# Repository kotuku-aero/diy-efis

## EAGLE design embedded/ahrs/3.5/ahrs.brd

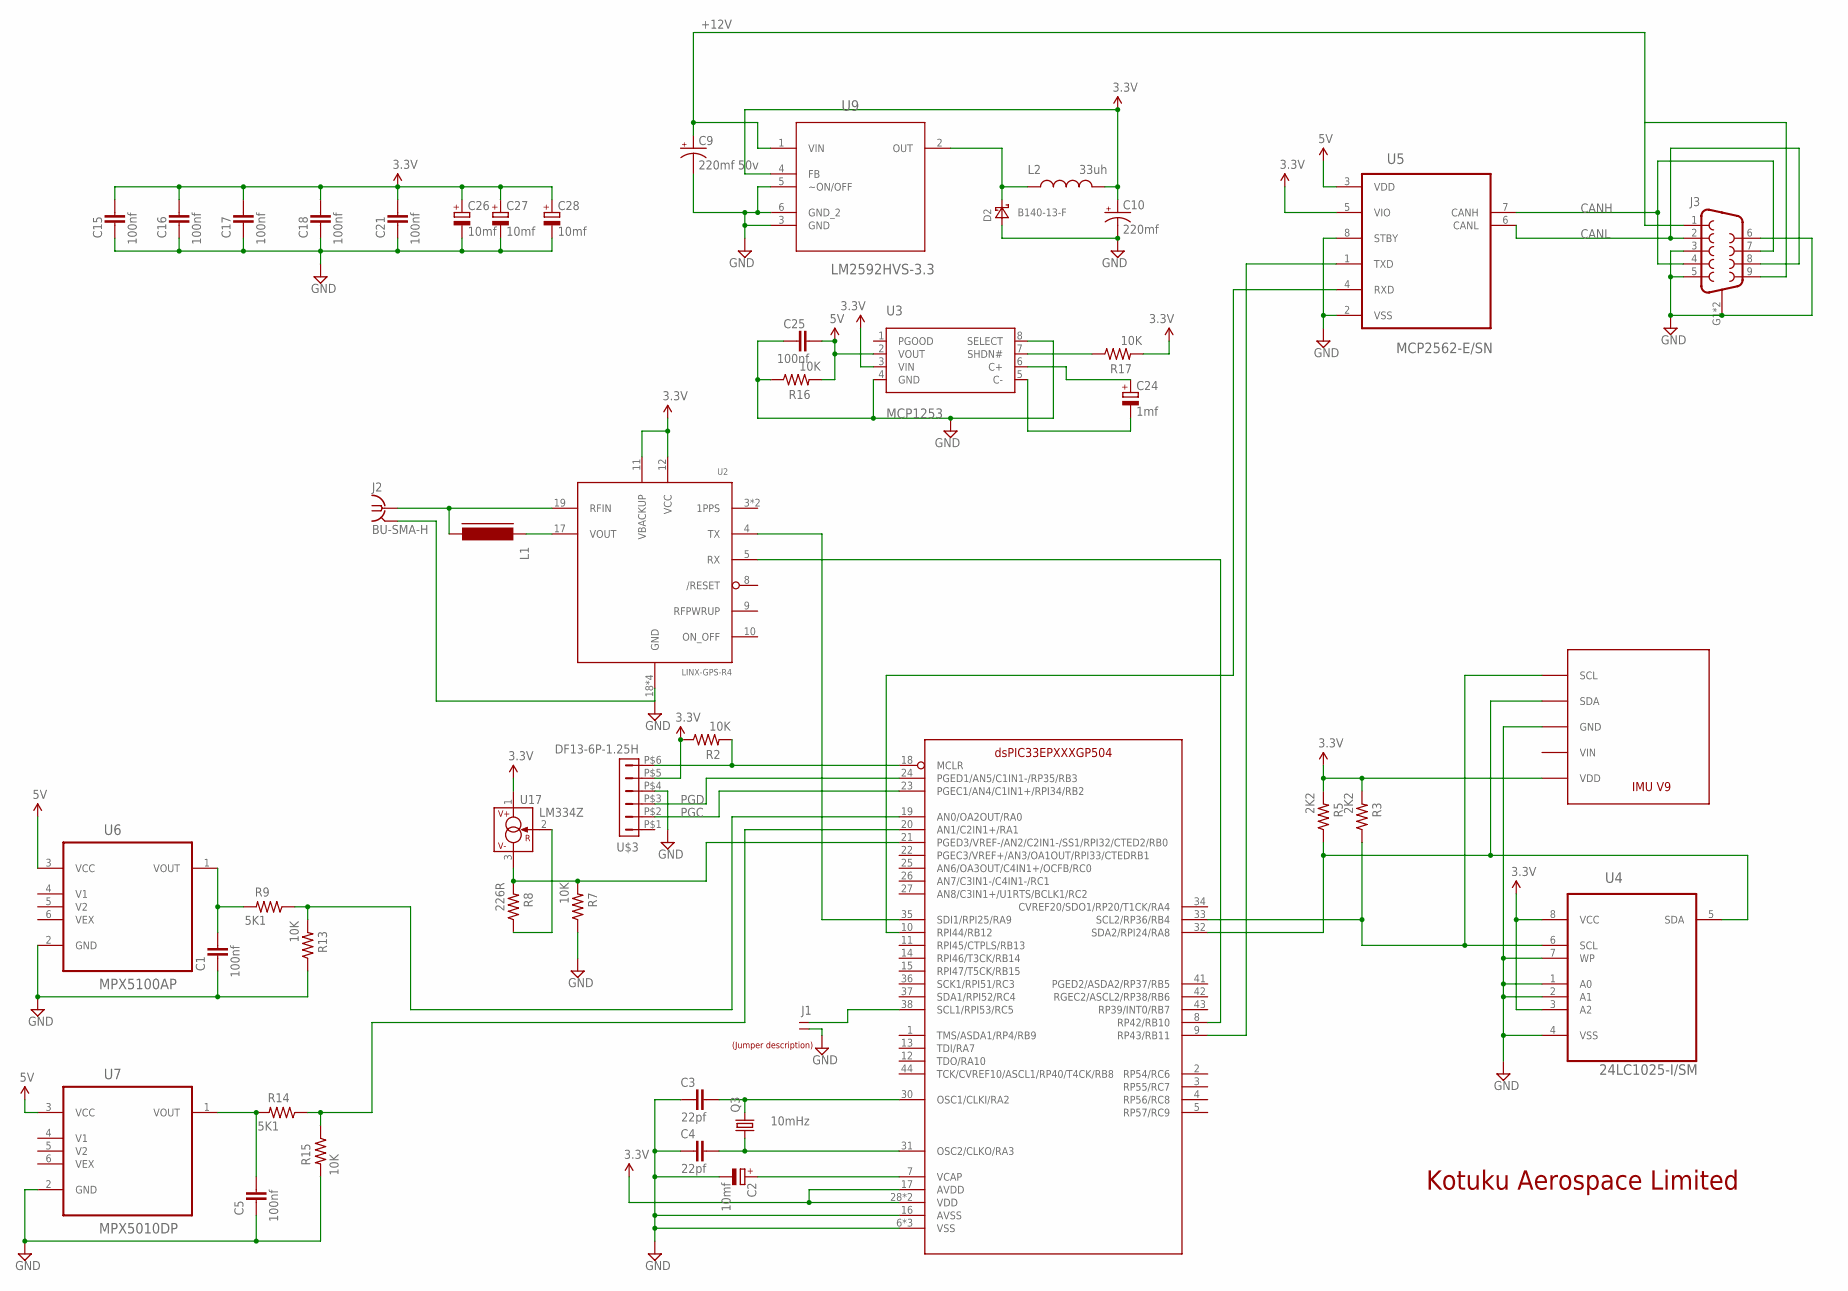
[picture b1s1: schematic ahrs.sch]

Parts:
C1, C5, C15, C16, C17, C18, C21, C25: 100nf; C805
C2, C26, C27, C28: 10mf; SMC_A
C3, C4: 22pf; C805
C9: 220mf 50v; EIA7343
C10: 220mf; EIA7343
C24: 1mf; SMC_A
D2: B140-13-F; SMA
J1: JUMPER-1X2
J2: BU-SMA-H; PARTNO 5-1814400-1
J3: DB9FEMALE; DB9; PARTNO 1734354-2
L1: FERRITE-PTH-10; L10; PARTNO BL01RN1A1D2B
L2: 33uh; 1812
Q3: 10mHz; HC49/S; PARTNO 9B-10.000MBBK-B
R2, R7, R13, R15, R16, R17: 10K; 0603-RES; PARTNO ERJ-3GEYJ103V
R3, R5: 2K2; 0603-RES; PARTNO ERJ-3GEYJ103V
R8: 226R; 0603-RES; PARTNO ERJ-3GEYJ103V
R9, R14: 5K1; 0603-RES; PARTNO ERJ-3GEYJ103V
U1: DSPIC33EPXXXGP504; TQFP44
U2: LINX-GPS-R4; LINX-R4; PARTNO RXM-GPS-R4-T
U3: MCP1253; MSOP8
U4: 24LC1025-I/SM; SOIC8-N_MC
U5: MCP2562-E/SN; SOIC-8N
U6: MPX5100AP; FREESCALE_CASE_867B-04
U7: MPX5010DP; FREESCALE_CASE_867B-04
U8: IMUV9
U9: LM2592HVS-3.3; TO170P1435X457-5N
U17: LM334Z; TO92; PARTNO LM334Z/NOPB
U$1: LABEL_JUMPER_1X2; JUMP2_DESC
U$3: DF13-6P-1.25H; DF13A-6P-1.25H

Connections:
3.3V: C10.A (+), C15.1, C16.1, C17.1, C18.1, C21.1, C26.+, C27.+, C28.+, L2.2, R2.1, R3.2, R5.2, R17.2, U1.17 (AVDD), U1.28 (VDD), U1.40 (VDD), U2.11 (VBACKUP), U2.12 (VCC), U3.3 (VIN), U4.3 (A2), U4.8 (VCC), U5.5 (VIO), U8.VDD, U9.4 (FB), U17.1 (V+), U$3.P$5 (5)
5V: C25.1, R16.2, U3.2 (VOUT), U5.3 (VDD), U6.3 (VCC), U7.3 (VCC)
!MCLR: R2.2, U1.18 (MCLR), U$3.P$6 (6)
+12V: C9.A (+), J3.1, J3.9, U9.1 (VIN)
CANH: J3.4, J3.7, U5.7 (CANH)
CANL: J3.2, J3.8, U5.6 (CANL)
GND: C1.2, C2.-, C3.2, C4.2, C5.2, C9.C (-), C10.C (-), C15.2, C16.2, C17.2, C18.2, C21.2, C25.2, C26.-, C27.-, C28.-, D2.A, J1.2, J2.2, J2.3 (2), J2.4 (2), J2.5 (2), J3.3, J3.5, J3.6, J3.G1 (SHIELD), J3.G2 (SHIELD), R7.1, R13.1, R15.2, R16.1, U1.6 (VSS), U1.16 (AVSS), U1.29 (VSS), U1.39 (VSS), U2.18 (GND), U2.20 (GND), U2.21 (GND), U2.22 (GND), U3.4 (GND), U3.8 (SELECT), U4.1 (A0), U4.2 (A1), U4.4 (VSS), U4.7 (WP), U5.2 (VSS), U5.8 (STBY), U6.2 (GND), U7.2 (GND), U8.GND, U9.3 (GND), U9.5 (~ON/OFF), U9.6 (GND_2), U$3.P$4 (4)
unnamed: L1.1, U2.17 (VOUT)
unnamed: J2.1, L1.2, U2.19 (RFIN)
unnamed: C2.+, U1.7 (VCAP)
unnamed: C3.1, Q3.2, U1.30 (OSC1/CLKI/RA2)
unnamed: R9.1, R13.2, U1.19 (AN0/OA2OUT/RA0)
unnamed: C1.1, R9.2, U6.1 (VOUT)
unnamed: R5.1, U1.32 (SDA2/RPI24/RA8), U4.5 (SDA), U8.SDA
unnamed: R3.1, U1.33 (SCL2/RP36/RB4), U4.6 (SCL), U8.SCL
unnamed: C5.1, R14.2, U7.1 (VOUT)
unnamed: D2.C, L2.1, U9.2 (OUT)
unnamed: R7.2, R8.2, U1.21 (PGED3/VREF-/AN2/C2IN1-/SS1/RPI32/CTED2/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), U17.3 (V-)
unnamed: U1.35 (SDI1/RPI25/RA9), U2.4 (TX)
unnamed: U1.8 (RP42/RB10), U2.5 (RX)
unnamed: R8.1, U17.2 (R)
unnamed: U1.10 (RPI44/RB12), U5.4 (RXD)
unnamed: J1.1, U1.38 (SCL1/RPI53/RC5)
unnamed: U1.9 (RP43/RB11), U5.1 (TXD)
unnamed: R17.1, U3.7 (SHDN#)
unnamed: C24.-, U3.5 (C-)
unnamed: C24.+, U3.6 (C+)
unnamed: C4.1, Q3.1, U1.31 (OSC2/CLKO/RA3)
PGC: U1.23 (PGEC1/AN4/C1IN1+/RPI34/RB2), U$3.P$2 (2)
PGD: U1.24 (PGED1/AN5/C1IN1-/RP35/RB3), U$3.P$3 (3)
PITOT: R14.1, R15.1, U1.20 (AN1/C2IN1+/RA1)
VIN: U8.VIN

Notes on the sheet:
Kotuku Aerospace Limited

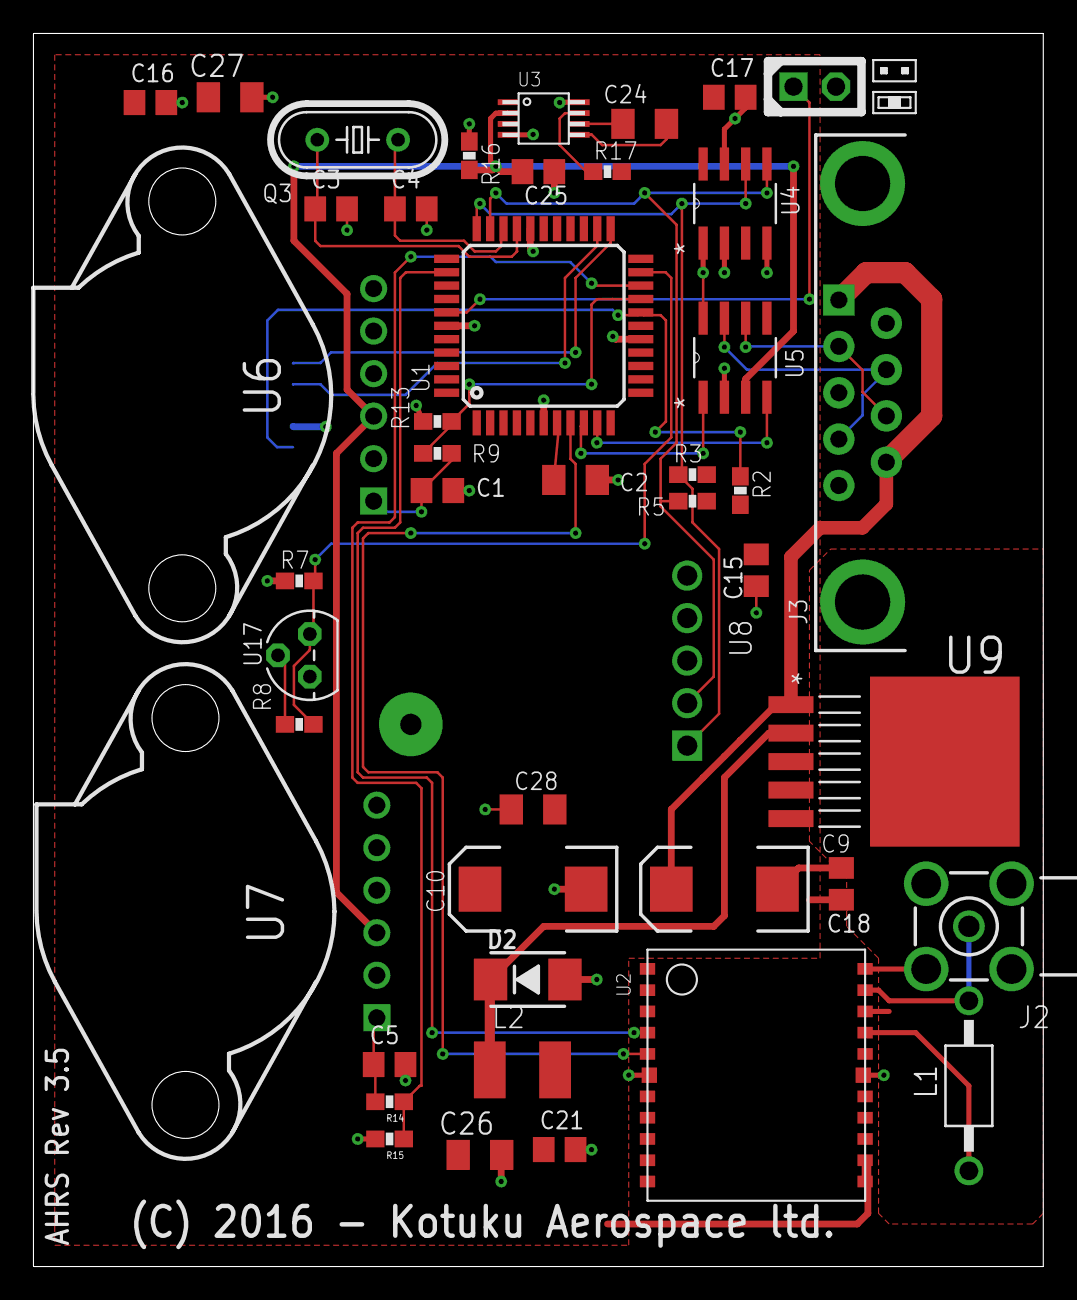
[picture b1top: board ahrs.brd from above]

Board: 2 copper layers, 60.3 x 73.7 mm, 47 parts (1 on the bottom side), 31 nets.

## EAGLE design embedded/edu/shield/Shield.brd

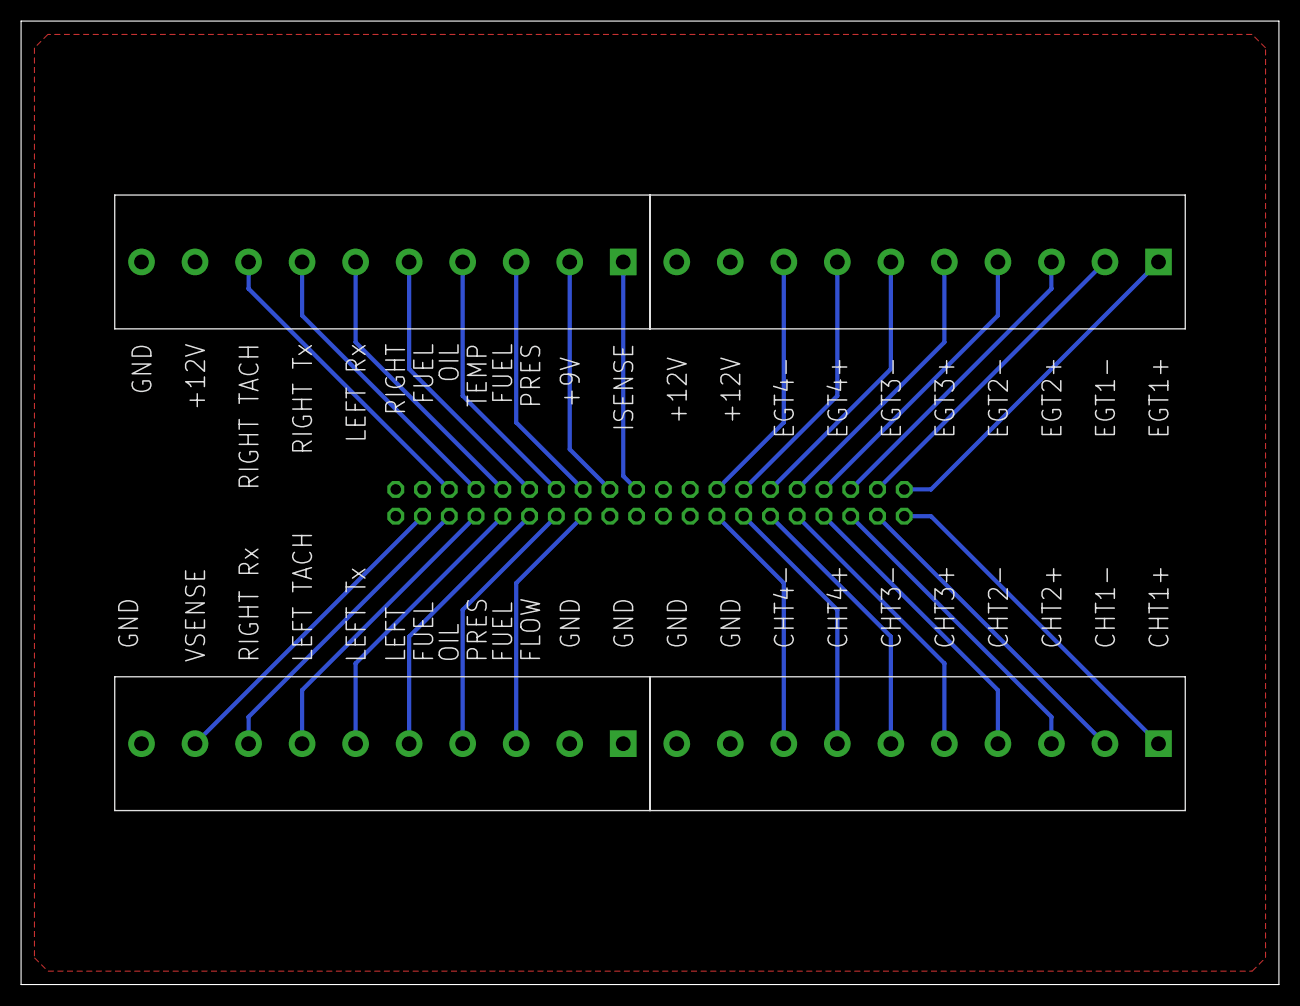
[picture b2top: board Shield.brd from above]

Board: 2 copper layers, 119.4 x 91.4 mm, 5 parts (1 on the bottom side), 33 nets.

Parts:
J1: 057-040-1
TB1, TB2, TB3, TB4: 282847-10

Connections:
+12V: J1.18, J1.20, J1.38, TB3.9, TB4.9, TB4.10
GND: J1.17, J1.19, J1.21, J1.23, J1.39, J1.40, TB1.1, TB1.2, TB1.10, TB2.9, TB2.10, TB3.10
unnamed: J1.1, TB2.1
unnamed: J1.3, TB2.2
unnamed: J1.5, TB2.3
unnamed: J1.7, TB2.4
unnamed: J1.9, TB2.5
unnamed: J1.11, TB2.6
unnamed: J1.13, TB2.7
unnamed: J1.15, TB2.8
unnamed: J1.2, TB4.1
unnamed: J1.4, TB4.2
unnamed: J1.6, TB4.3
unnamed: J1.8, TB4.4
unnamed: J1.12, TB4.6
unnamed: J1.14, TB4.7
unnamed: J1.16, TB4.8
unnamed: J1.25, TB1.3
unnamed: J1.27, TB1.4
unnamed: J1.29, TB1.5
unnamed: J1.31, TB1.6
unnamed: J1.33, TB1.7
unnamed: J1.35, TB1.8
unnamed: J1.37, TB1.9
unnamed: J1.10, TB4.5
unnamed: J1.22, TB3.1
unnamed: J1.24, TB3.2
unnamed: J1.26, TB3.3
unnamed: J1.28, TB3.4
unnamed: J1.30, TB3.5
unnamed: J1.32, TB3.6
unnamed: J1.34, TB3.7
unnamed: J1.36, TB3.8

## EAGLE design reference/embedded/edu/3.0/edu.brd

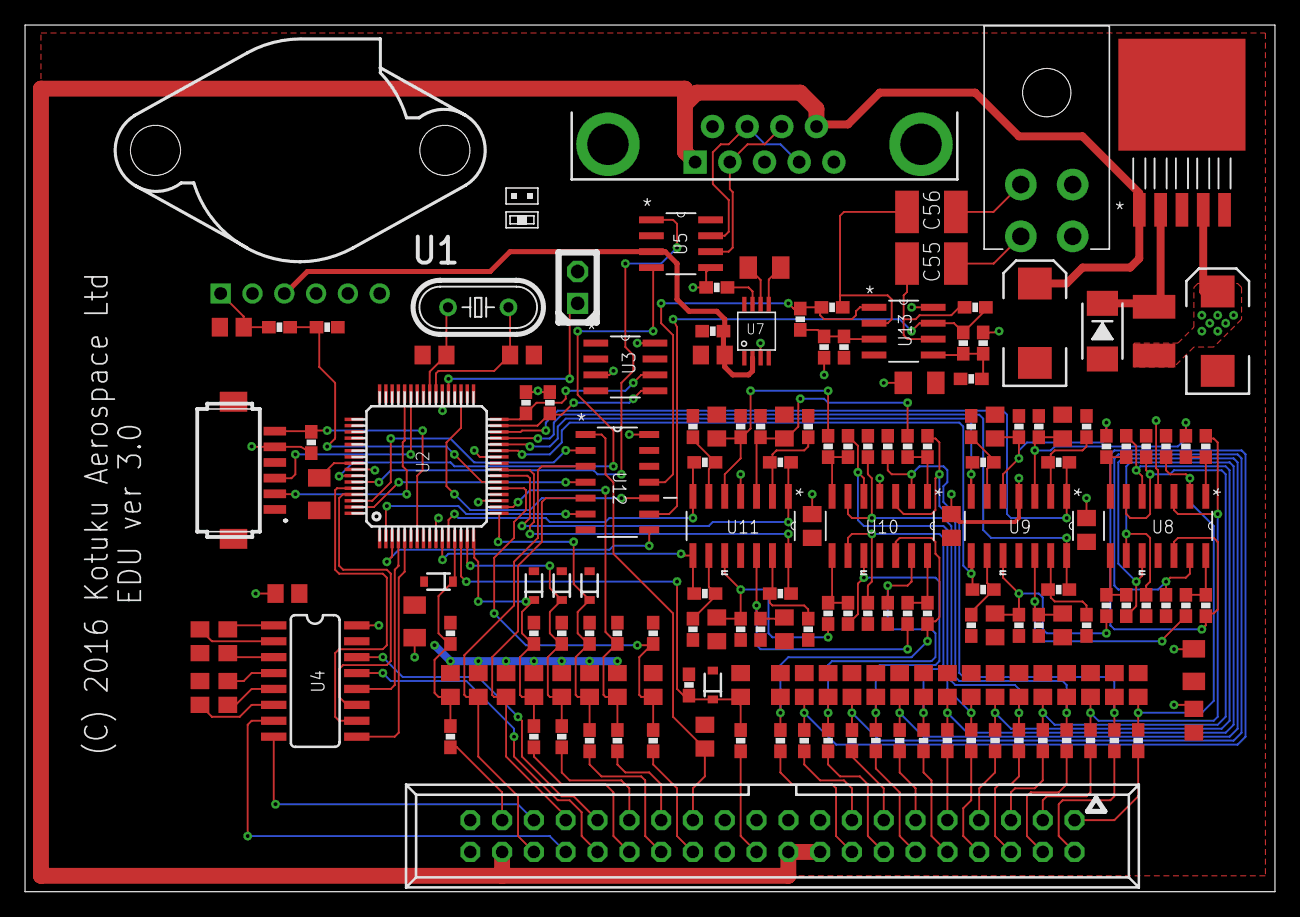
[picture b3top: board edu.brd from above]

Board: 2 copper layers, 99.8 x 69.2 mm, 176 parts (0 on the bottom side), 131 nets.

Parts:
C1, C2, C3, C4, C5, C7, C8, C9, C10, C11, C12, C13, C14, C15, C16, C17, C18, C19, C20, C21, C22, C23, C27, C28, C29, C30, C33, C34, C35, C36, C37, C38, C39, C40, C41, C42, C43, C44, C45, C46, C47, C48, C49, C50, C51: 100nf; C805
C6: 1mf; SMC_A
C24, C52, C53, C54: 10mf; SMC_A
C25, C26: 22pf; C805
C31: 220mf; EIA7343
C32: 220mf 50v; EIA7343
C55, C56: 100nF; 1812
D2: B140-13-F; SMA
J1: M20-9770246; JUMPER-1X2
J2: DB9
J3: DF13-6P-1.25H; DF13A-6P-1.25H
J4: 1-770968-1
L2: 33uh; 1812
Q1: 10mHz; HC49/S
R1, R2, R3, R4, R7, R8, R15, R16, R18, R22, R24, R26, R28, R31, R32, R34, R37, R38, R53, R55, R57, R58, R59, R62, R63, R66, R67: 10K; 0603-RES
R5, R6, R9, R11, R13, R14, R17, R19, R39, R40, R60, R61, R64, R65, R68, R69: 100K; 0603-RES
R10, R12, R20, R54, R56: 27K; 0603-RES
R21, R25, R41, R43, R45, R47, R49, R51, R70, R72, R74, R76, R78, R80, R82, R84: 1K; 0603-RES
R23, R27, R42, R44, R46, R48, R50, R52, R71, R73, R75, R77, R79, R81, R83, R85: 7K15; 0603-RES
R29, R30: 2K2; 0603-RES
R33, R35, R36: 5K15; 0603-RES
R86, R87, R88, R90, R91, R92: 470K; 0603-RES
R89, R93: 1M1; 0603-RES
U1: MPX5100AP; FREESCALE_CASE_867B-04
U2: DSPIC33EPXXXGP506; TQFP64-10X10
U3: 24LC1025-I/SM; SOIC8-N_MC
U4: MAX232SOIC16; SO016
U5: MCP2562-E/SN; SOIC-8N
U6: LM2592HVS-3.3; TO170P1435X457-5N
U7: MCP1253; MSOP8
U8, U9, U10, U11: MCP619-I/SL; SOIC127P600X175-14N
U12: 74LCX14M; SOIC127P600X175-14N
U13: MCP617-I/SN; SOIC127P600X175-8N
U$5: LABEL_JUMPER_1X2; JUMP2_DESC
X2: 057-040-1
Z1, Z2, Z3, Z4, Z5: BZT52C3V3S-7-F; SOD-323

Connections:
3.3V: C31.A, C47.1, C48.1, C49.1, C50.1, C51.1, C52.+, C53.+, C54.+, J3.P$5, L2.2, R18.1, R24.2, R29.2, R30.2, R87.2, R92.2, U2.10, U2.19, U2.26, U2.38, U2.57, U3.3, U3.8, U4.16, U5.5, U6.4, U7.3, U8.4, U9.4, U10.4, U11.4, U12.14, U13.8
5V: C30.1, R22.2, U1.3, U5.3, U7.2
!MCLR: J3.P$6, R18.2, U2.7
#FUEL_FLOW: U2.62, U12.2
#LEFT_TACH: U2.2, U12.6
#RIGHT_TACH: U2.63, U12.4
+12V: C32.A, J2.1, J2.9, U6.1, X2.18, X2.20, X2.38
CANH: J2.4, J2.7, U5.7
CANL: J2.2, J2.8, U5.6
CHT1: R27.1, U2.30, U9.1
CHT1+: R2.2, X2.1
CHT1-: R1.2, X2.3
CHT1OA+: C10.1, R21.1, R23.2, U9.3
CHT1OA-: R25.1, R27.2, U9.2
CHT2: R44.1, U2.28, U9.7
CHT2+: R4.2, X2.5
CHT2-: R3.2, X2.7
CHT2OA+: C15.1, R41.1, R42.2, U9.5
CHT2OA-: R43.1, R44.2, U9.6
CHT3: R52.1, U2.27, U9.8
CHT3+: R8.2, X2.9
CHT3-: R7.2, X2.11
CHT3OA+: C17.1, R49.1, R50.2, U9.10
CHT3OA-: R51.1, R52.2, U9.9
CHT4: R48.1, U2.29, U9.14
CHT4+: R16.2, X2.13
CHT4+OA: C9.1, R16.1, R17.2, U8.13
CHT4-: R15.2, X2.15
CHT4-OA: C8.1, R15.1, R19.2, U8.12
CHT4OA+: C16.1, R45.1, R46.2, U9.12
CHT4OA-: R47.1, R48.2, U9.13
EGT1: R73.1, U2.23, U11.1
EGT1+: R32.2, X2.2
EGT1-: R31.2, X2.4
EGT1OA+: C40.1, R70.1, R71.2, U11.3
EGT1OA-: R72.1, R73.2, U11.2
EGT2: R77.1, U2.12, U11.7
EGT2+: R59.2, X2.6
EGT2-: R58.2, X2.8
EGT2OA+: C44.1, R74.1, R75.2, U11.5
EGT2OA-: R76.1, R77.2, U11.6
EGT3: R85.1, U2.11, U11.8
EGT3+: R63.2, X2.10
EGT3-: R62.2, X2.12
EGT3OA+: C46.1, R82.1, R83.2, U11.10
EGT3OA-: R84.1, R85.2, U11.9
EGT4: R81.1, U2.24, U11.14
EGT4+: R67.2, X2.14
EGT4-: R66.2, X2.16
EGT4OA+: C45.1, R78.1, R79.2, U11.12
EGT4OA-: R80.1, R81.2, U11.13
FUEL_FLOW: C12.2, U12.1, X2.25
FUEL_PRESSURE: R35.1, X2.26
GND: C1.2, C2.2, C3.2, C4.2, C5.2, C7.2, C8.2, C9.2, C10.2, C11.2, C12.1, C13.1, C14.1, C15.2, C16.2, C17.2, C18.1, C19.1, C20.1, C21.1, C22.1, C23.1, C24.-, C25.2, C26.2, C27.2, C28.2, C29.2, C30.2, C31.C, C32.C, C34.2, C35.1, C36.2, C37.2, C38.2, C39.2, C40.2, C42.1, C43.1, C44.2, C45.2, C46.2, C47.2, C48.2, C49.2, C50.2, C51.2, C52.-, C53.-, C54.-, D2.A, J1.2, J2.3, J2.5, J2.6, J2.G1, J2.G2, J3.P$4, J4.P$2, J4.P$4, R5.1, R9.1, R13.1, R17.1, R22.1, R23.1, R25.2, R26.2, R28.2, R34.1, R37.1, R38.1, R39.1, R42.1, R43.2, R46.1, R47.2, R50.1, R51.2, R53.2, R55.2, R57.2, R60.1, R64.1, R68.1, R71.1, R72.2, R75.1, R76.2, R79.1, R80.2, R83.1, R84.2, R88.1, R91.1, U1.2, U2.9, U2.20, U2.25, U2.41, U3.1, U3.2, U3.4, U3.7, U4.15, U5.2, U5.8, U6.3, U6.5, U6.6, U7.4, U7.8, U8.11, U9.11, U10.11, U11.11, U12.7, U12.13, U13.4, X2.17, X2.19, X2.21, X2.23, X2.39, X2.40, Z1.2, Z2.2, Z3.2, Z4.2, Z5.2
ISENSE: R56.1, X2.22
LEFT_FUEL: R54.1, X2.29
LEFT_RXD: U4.13, X2.32
LEFT_TACH: C23.2, U12.5, X2.33
LEFT_TXD: U4.14, X2.31
unnamed: C1.1, R1.1, R11.2, U8.3
unnamed: R24.1, U7.7
unnamed: C2.1, R2.1, R9.2, U8.2
unnamed: C18.2, R20.2, R53.1, U2.13, Z1.1
unnamed: C33.1, U4.1
unnamed: C33.2, U4.3
unnamed: C41.2, U4.4
unnamed: C22.2, R10.2, R28.1, U2.17, Z5.1
unnamed: C41.1, U4.5
unnamed: C42.2, U4.2
unnamed: C43.2, U4.6
unnamed: D2.C, L2.1, U6.2
unnamed: R33.2, R34.2, U2.22
unnamed: C35.2, R35.2, R37.2, U2.21
unnamed: C14.2, R36.2, R38.2, U2.18
unnamed: C25.1, Q1.2, U2.39
unnamed: R11.1, R21.2, U8.1
unnamed: C3.1, R3.1, R6.2, U8.5
unnamed: C4.1, R4.1, R5.2, U8.6
unnamed: C7.1, R8.1, R13.2, U8.9
unnamed: C55.2, J4.P$1
unnamed: C56.2, J4.P$3
unnamed: R6.1, R41.2, U8.7
unnamed: R14.1, R49.2, U8.8
unnamed: C5.1, R7.1, R14.2, U8.10
unnamed: R19.1, R45.2, U8.14
unnamed: C27.1, R31.1, R40.2, U10.3
unnamed: R86.2, R89.2, U12.9, U13.7
unnamed: C55.1, R89.1, U13.6
unnamed: C56.1, R93.1, U13.2
unnamed: C24.+, U2.56
unnamed: R90.2, R93.2, U12.11, U13.1
unnamed: U2.3, U12.8
unnamed: U2.35, U12.10
unnamed: J1.1, U2.37
unnamed: C6.-, U7.5
unnamed: C6.+, U7.6
unnamed: R30.1, U2.32, U3.6
unnamed: R88.2, R90.1, R92.1, U13.3
unnamed: R29.1, U2.31, U3.5
unnamed: C19.2, R12.2, R26.1, U2.16, Z2.1
unnamed: C20.2, R54.2, R55.1, U2.15, Z3.1
unnamed: C21.2, R56.2, R57.1, U2.14, Z4.1
unnamed: U2.59, U5.1
unnamed: U2.61, U4.11
unnamed: U2.60, U4.10
unnamed: U2.4, U4.12
unnamed: U2.5, U4.9
unnamed: U2.58, U5.4
unnamed: C28.1, R32.1, R39.2, U10.2
unnamed: C29.1, R58.1, R61.2, U10.5
unnamed: C34.1, R59.1, R60.2, U10.6
unnamed: C38.1, R66.1, R69.2, U10.12
unnamed: C11.1, R33.1, U1.1
unnamed: C36.1, R62.1, R65.2, U10.10
unnamed: C37.1, R63.1, R64.2, U10.9
unnamed: C39.1, R67.1, R68.2, U10.13
unnamed: R40.1, R70.2, U10.1
unnamed: R61.1, R74.2, U10.7
unnamed: R65.1, R82.2, U10.8
unnamed: R86.1, R87.1, R91.2, U13.5
unnamed: C26.1, Q1.1, U2.40
unnamed: R69.1, R78.2, U10.14
OIL_PRESSURE: R36.1, X2.27
OIL_TEMPERATURE: R10.1, X2.28
PGC: J3.P$2, U2.44
PGD: J3.P$3, U2.43
RIGHT_FUEL: R12.1, X2.30
RIGHT_RXD: U4.8, X2.35
RIGHT_TACH: C13.2, U12.3, X2.36
RIGHT_TXD: U4.7, X2.34
VSENSE: R20.1, X2.37

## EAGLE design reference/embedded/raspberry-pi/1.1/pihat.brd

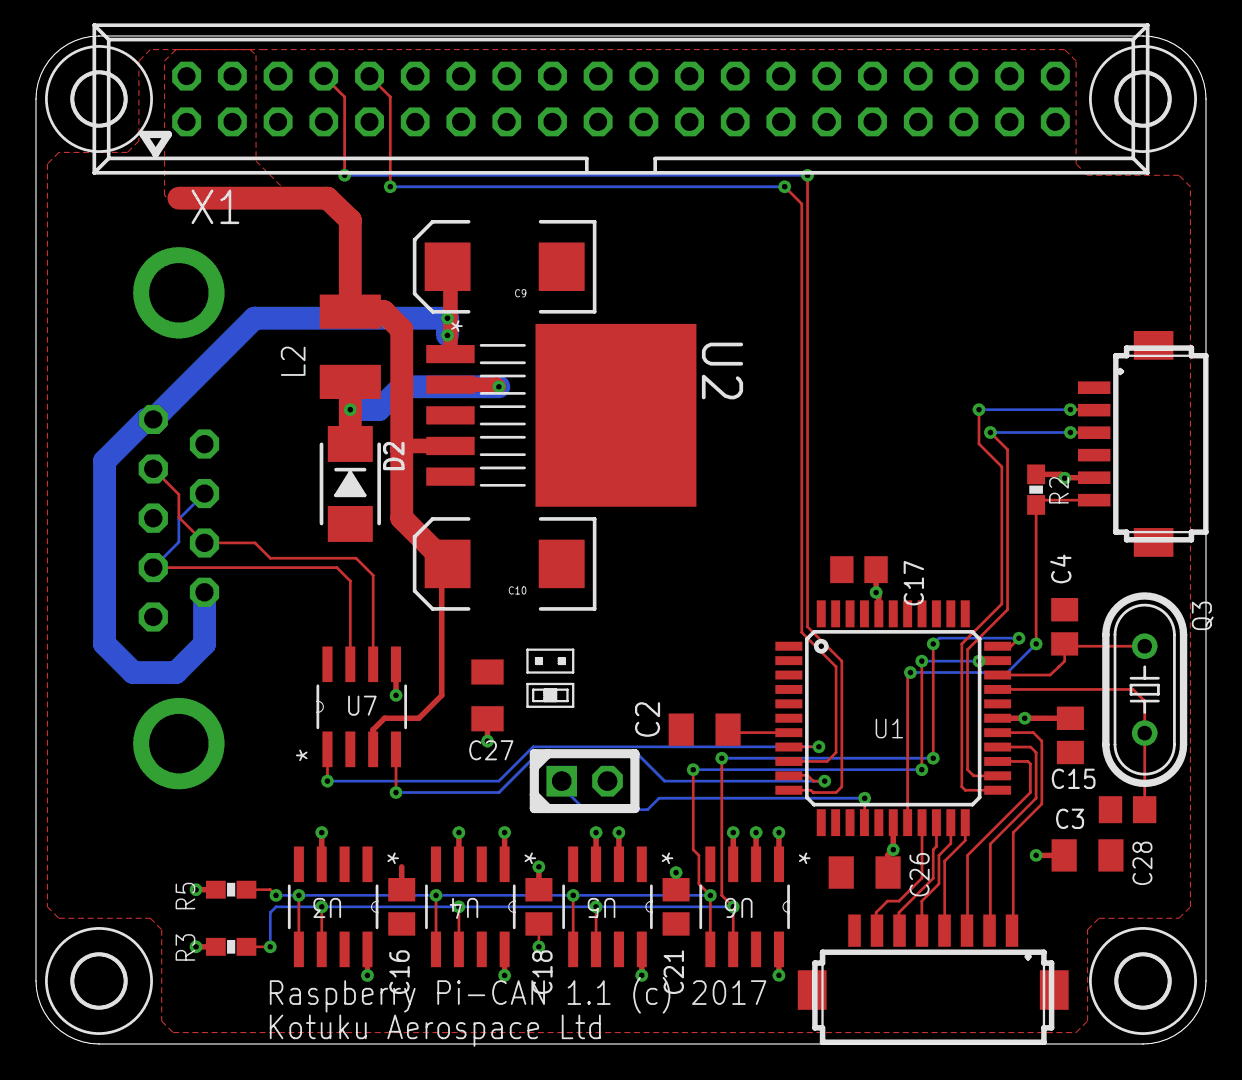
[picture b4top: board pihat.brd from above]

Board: 2 copper layers, 65.0 x 56.0 mm, 36 parts (1 on the bottom side), 27 nets.

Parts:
C2, C26, C27, C28: 10mf; SMC_A
C3, C4: 22pf; C805
C9: 220mf 50v; EIA7343
C10: 220mf; EIA7343
C15, C16, C17, C18, C21: 100nf; C805
D2: B140-13-F; SMA
J1: M09VP
J3: DF13-6P-1.25H; DF13A-6P-1.25H
J4: JUMPER-1X2
L2: 33uh; 1812
M1, M2, M3, M4: MOUNT-HOLE2.8; 2,8
Q3: 10mHz; HC49/S
R2: 10K; 0603-RES
R3, R5: 2K2; 0603-RES
U1: DSPIC33EPXXXGP504; TQFP44
U2: LM2592HVS-5.0; TO170P1435X457-5N
U3, U4, U5, U6: 24LC1025-I/SM; SOIC8-N_MC
U7: MCP2562-E/SN; SOIC-8N
U$1: LABEL_JUMPER_1X2; JUMP2_DESC
U$2: DF13-8P-1.25H; DF13A-8P-1.25H
X1: 057-040-1

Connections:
3.3V: C15.1, C16.1, C17.1, C18.1, C21.1, C26.+, C27.+, C28.+, J3.P$5, R2.1, R3.2, R5.2, U1.17, U1.28, U1.40, U3.3, U3.8, U4.1, U4.3, U4.8, U5.2, U5.3, U5.8, U6.1, U6.2, U6.3, U6.8, U7.5, X1.1, X1.17
5V: C10.A, L2.2, U2.4, U7.3, X1.2, X1.4
!MCLR: J3.P$6, R2.2, U1.18
+12V: C9.A, J1.1, J1.9, U2.1
CANH: J1.4, J1.7, U7.7
CANL: J1.2, J1.8, U7.6
GND: C2.-, C3.2, C4.2, C9.C, C10.C, C15.2, C16.2, C17.2, C18.2, C21.2, C26.-, C27.-, C28.-, D2.A, J1.3, J1.5, J1.6, J1.G1, J3.P$4, J4.2, U1.6, U1.16, U1.29, U1.39, U2.3, U2.5, U2.6, U3.1, U3.2, U3.4, U3.7, U4.2, U4.4, U4.7, U5.1, U5.4, U5.7, U6.4, U6.7, U7.2, U7.8, U$2.P$8, X1.6, X1.9, X1.14, X1.20, X1.25, X1.30, X1.34, X1.39
unnamed: U1.19, U$2.P$7
unnamed: U1.20, U$2.P$6
unnamed: U1.21, U$2.P$5
unnamed: U1.22, U$2.P$4
unnamed: U1.25, U$2.P$3
unnamed: U1.26, U$2.P$2
unnamed: U1.27, U$2.P$1
unnamed: D2.C, L2.1, U2.2
unnamed: C3.1, Q3.2, U1.30
unnamed: U1.10, U7.4
unnamed: C2.+, U1.7
unnamed: U1.8, U7.1
unnamed: C4.1, Q3.1, U1.31
PGC: J3.P$2, U1.23
PGD: J3.P$3, U1.24
RESET#: J4.1, U1.15
RXD0: U1.9, X1.10
SCL: R3.1, U1.33, U3.6, U4.6, U5.6, U6.6
SDA: R5.1, U1.32, U3.5, U4.5, U5.5, U6.5
TXD0: U1.11, X1.8

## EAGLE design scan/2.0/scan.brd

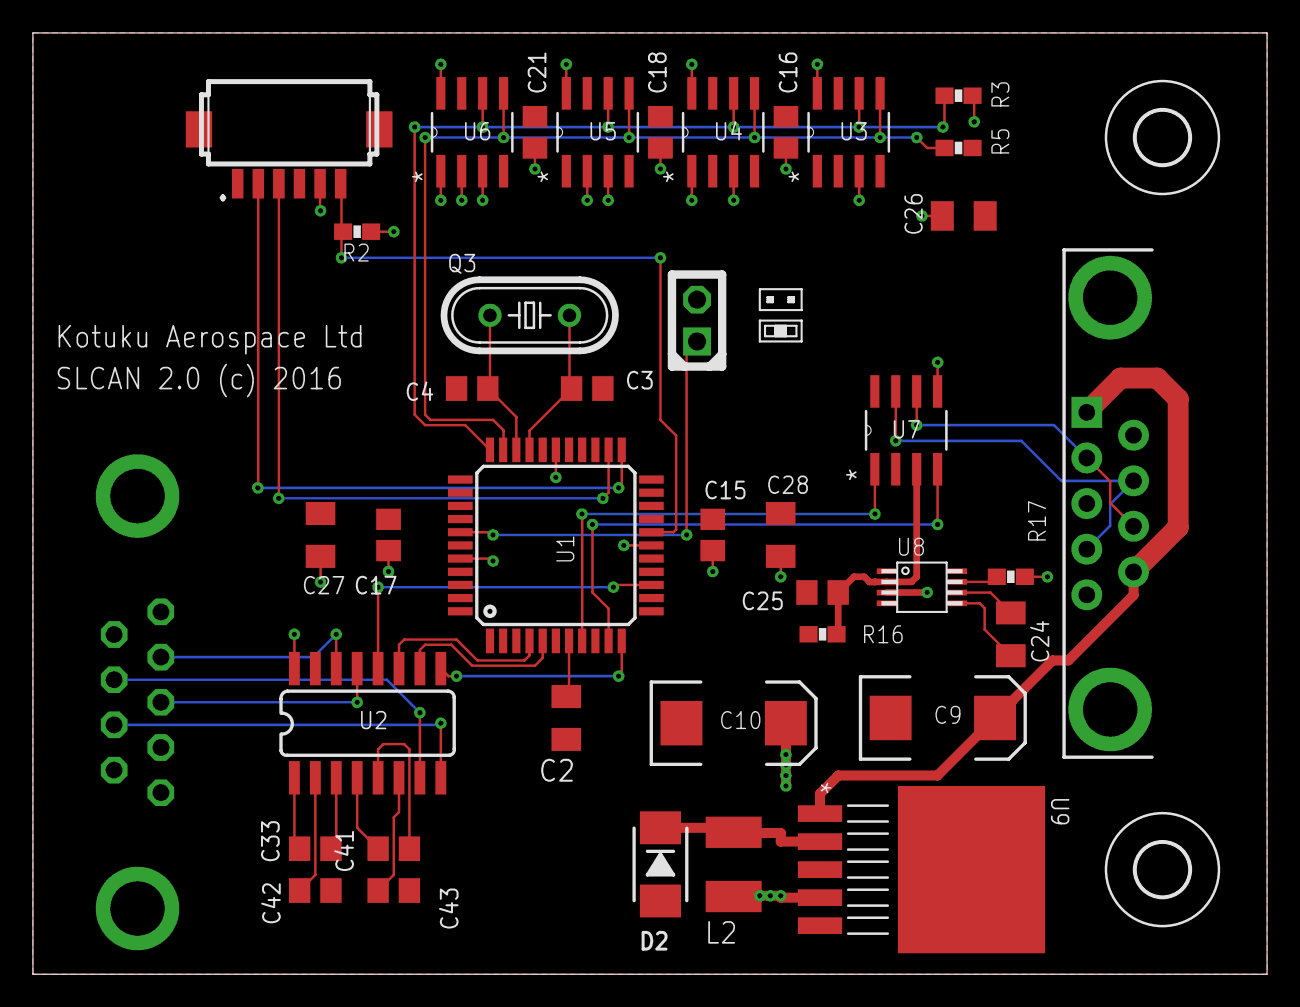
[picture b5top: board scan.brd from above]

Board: 2 copper layers, 74.9 x 57.1 mm, 43 parts (1 on the bottom side), 35 nets.

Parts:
C2, C26, C27, C28: 10mf; SMC_A
C3, C4: 22pf; C805
C9: 220mf 50v; EIA7343
C10: 220mf; EIA7343
C15, C16, C17, C18, C21, C25, C33, C41, C42, C43: 100nf; C805
C24: 1mf; SMC_A
D2: B140-13-F; SMA
H1, H2: MOUNT-HOLE3.2; 3,2
J1: F09VP
J2: DB9
J3: DF13-6P-1.25H; DF13A-6P-1.25H
J4: JUMPER-1X2
L2: 33uh; 1812
Q3: 10mHz; HC49/S
R2, R16, R17: 10K; 0603-RES
R3, R5: 2K2; 0603-RES
U1: DSPIC33EPXXXGP504; TQFP44
U2: MAX232SOIC16; SO016
U3, U4, U5, U6: 24LC1025-I/SM; SOIC8-N_MC
U7: MCP2562-E/SN; SOIC-8N
U8: MCP1253; MSOP8
U9: LM2592HVS-3.3; TO170P1435X457-5N
U$1: LABEL_JUMPER_1X2; JUMP2_DESC

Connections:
3.3V: C10.A, C15.1, C16.1, C17.1, C18.1, C21.1, C26.+, C27.+, C28.+, J3.P$5, L2.2, R2.1, R3.2, R5.2, R17.2, U1.17, U1.28, U1.40, U2.16, U3.3, U3.8, U4.1, U4.3, U4.8, U5.2, U5.3, U5.8, U6.1, U6.2, U6.3, U6.8, U7.5, U8.3, U9.4
5V: C25.1, R16.2, U7.3, U8.2
!MCLR: J3.P$6, R2.2, U1.18
+12V: C9.A, J2.1, J2.9, U9.1
CANH: J2.4, J2.7, U7.7
CANL: J2.2, J2.8, U7.6
GND: C2.-, C3.2, C4.2, C9.C, C10.C, C15.2, C16.2, C17.2, C18.2, C21.2, C25.2, C26.-, C27.-, C28.-, C42.1, C43.1, D2.A, J1.5, J1.G1, J2.3, J2.5, J2.6, J2.G1, J2.G2, J3.P$4, J4.2, R16.1, U1.6, U1.16, U1.29, U1.39, U2.15, U3.1, U3.2, U3.4, U3.7, U4.2, U4.4, U4.7, U5.1, U5.4, U5.7, U6.4, U6.7, U7.2, U7.8, U8.4, U8.8, U9.3, U9.5, U9.6
unnamed: J1.2, U2.14
unnamed: U1.5, U2.10
unnamed: U1.4, U2.11
unnamed: J1.3, U2.13
unnamed: J1.8, U2.8
unnamed: J1.7, U2.7
unnamed: U1.11, U2.9
unnamed: U1.14, U2.12
unnamed: C33.1, U2.1
unnamed: C33.2, U2.3
unnamed: C3.1, Q3.2, U1.30
unnamed: C41.2, U2.4
unnamed: C41.1, U2.5
unnamed: D2.C, L2.1, U9.2
unnamed: U1.10, U7.4
unnamed: C2.+, U1.7
unnamed: U1.8, U7.1
unnamed: C42.2, U2.2
unnamed: C43.2, U2.6
unnamed: J4.1, U1.38
unnamed: R17.1, U8.7
unnamed: C24.-, U8.5
unnamed: C24.+, U8.6
unnamed: C4.1, Q3.1, U1.31
PGC: J3.P$2, U1.23
PGD: J3.P$3, U1.24
SCL: R3.1, U1.33, U3.6, U4.6, U5.6, U6.6
SDA: R5.1, U1.32, U3.5, U4.5, U5.5, U6.5

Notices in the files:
embedded/ahrs/3.5/ahrs.brd:
(C) 2016 - Kotuku Aerospace ltd.
reference/embedded/raspberry-pi/1.1/pihat.brd:
Raspberry Pi-CAN 1.1 (c) 2017
scan/2.0/scan.brd:
SLCAN 2.0 (c) 2016
parts and their libraries:
SparkFun-Connectors: Licensing: Creative Commons ShareAlike 4.0 International - https://creativecommons.org/licenses/by-sa/4.0
